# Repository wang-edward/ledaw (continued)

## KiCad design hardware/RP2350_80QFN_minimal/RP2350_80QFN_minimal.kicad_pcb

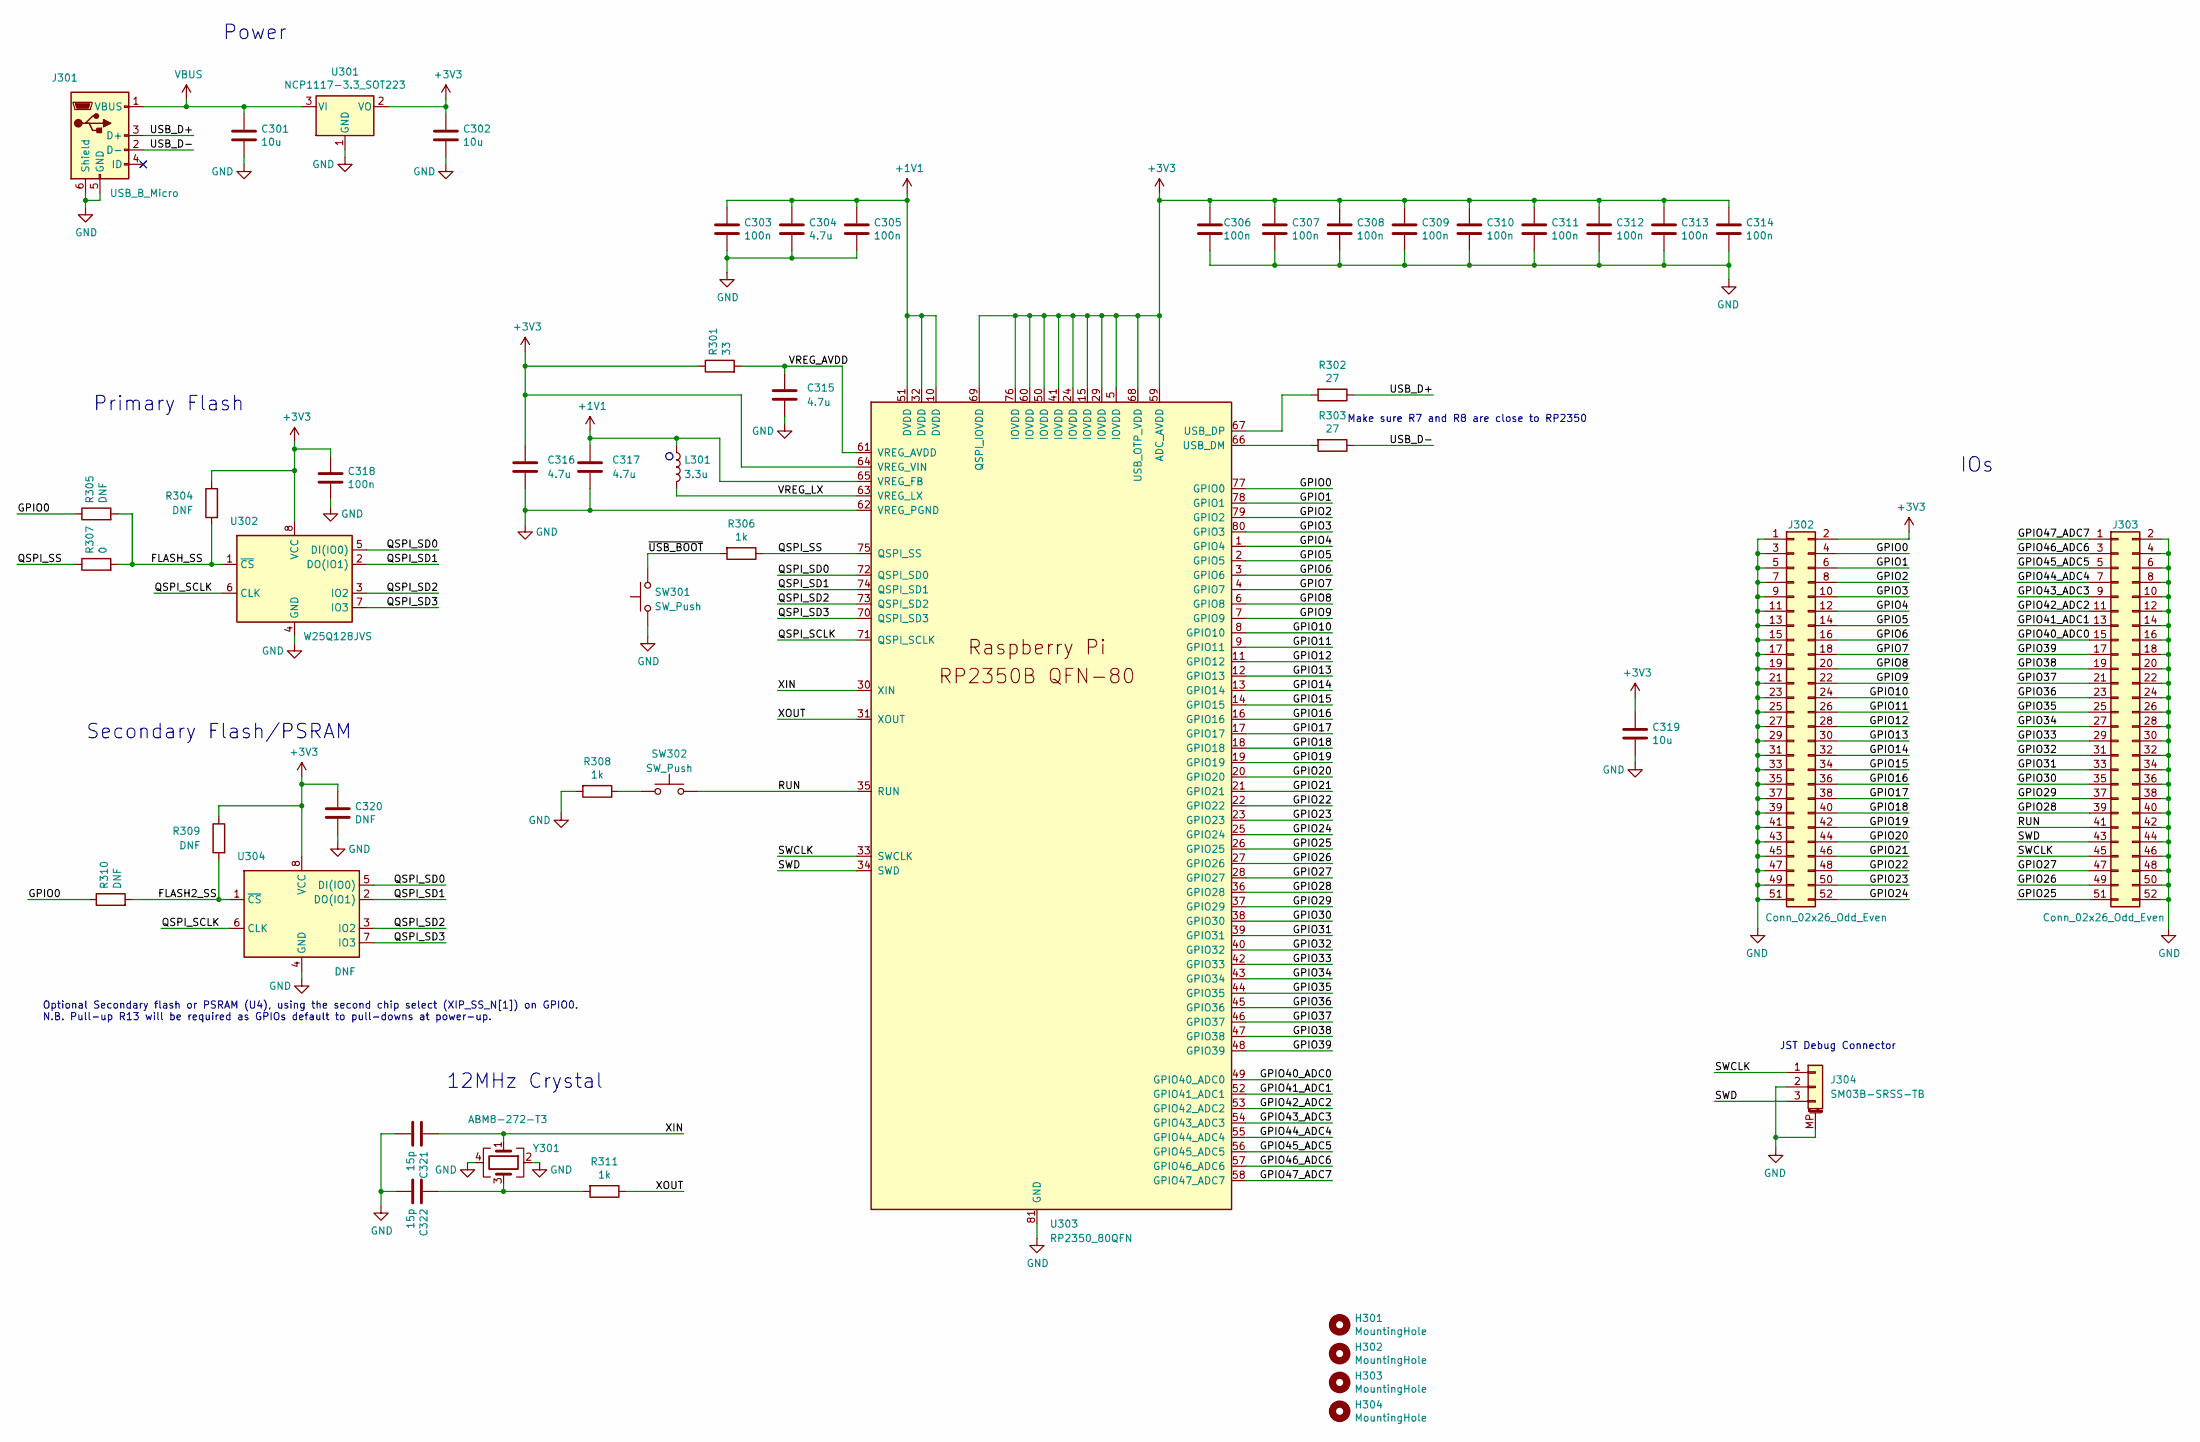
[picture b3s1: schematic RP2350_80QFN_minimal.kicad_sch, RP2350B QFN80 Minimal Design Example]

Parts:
C301, C302, C319: 10u; C_0805_2012Metric
C303, C305, C306, C307, C308, C309, C310, C311, C312, C313, C314, C318: 100n; C_0402_1005Metric
C304, C315: 4.7u; C_0402_1005Metric
C316, C317: 4.7u; C_0402_1005Metric_small_pads
C320: DNF; C_0402_1005Metric
C321, C322: 15p; C_0402_1005Metric
H301, H302, H303, H304: MountingHole; MountingHole_2.7mm_M2.5
J301: USB_B_Micro; USB_Micro-B_Amphenol_10103594-0001LF_Horizontal
J302, J303: Conn_02x26_Odd_Even; PinHeader_2x26_P2.54mm_Vertical
J304: SM03B-SRSS-TB; JST_SH_SM03B-SRSS-TB_1x03-1MP_P1.00mm_Horizontal
L301: 3.3u; L_pol_2016
R301: 33; R_0402_1005Metric
R302, R303: 27; R_0402_1005Metric
R304, R305, R309, R310: DNF; R_0402_1005Metric
R306, R308, R311: 1k; R_0402_1005Metric
R307: 0; R_0402_1005Metric
SW301, SW302: SW_Push; SW_Push_1P1T_NO_Vertical_Wuerth_434133025816
U301: NCP1117-3.3_SOT223; SOT-223-3_TabPin2
U302: W25Q128JVS; SOIC-8_5.23x5.23mm_P1.27mm
U303: RP2350_80QFN; RP2350-QFN-80-1EP_10x10_P0.4mm_EP3.4x3.4mm_ThermalVias
U304: DNF; SOIC-8_5.23x5.23mm_P1.27mm
Y301: ABM8-272-T3; Crystal_SMD_3225-4Pin_3.2x2.5mm

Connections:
+1V1: C303.1, C304.1, C305.1, C317.1, L301.1, U303.10 (DVDD), U303.32 (DVDD), U303.51 (DVDD), U303.65 (VREG_FB)
+3V3: C302.1, C306.1, C307.1, C308.1, C309.1, C310.1, C311.1, C312.1, C313.1, C314.1, C316.1, C318.1, C319.1, C320.1, J302.2, R301.1, R304.1, R309.1, U301.2 (VO), U302.8 (VCC), U303.5 (IOVDD), U303.15 (IOVDD), U303.24 (IOVDD), U303.29 (IOVDD), U303.41 (IOVDD), U303.50 (IOVDD), U303.59 (ADC_AVDD), U303.60 (IOVDD), U303.64 (VREG_VIN), U303.68 (USB_OTP_VDD), U303.69 (QSPI_IOVDD), U303.76 (IOVDD), U304.8 (VCC)
/FLASH2_SS: R309.2, R310.2, U304.1 (~CS)
/FLASH_SS: R304.2, R305.2, R307.2, U302.1 (~CS)
/GPIO0: J302.4, R305.1, R310.1, U303.77 (GPIO0)
/GPIO1: J302.6, U303.78 (GPIO1)
/GPIO2: J302.8, U303.79 (GPIO2)
/GPIO3: J302.10, U303.80 (GPIO3)
/GPIO4: J302.12, U303.1 (GPIO4)
/GPIO5: J302.14, U303.2 (GPIO5)
/GPIO6: J302.16, U303.3 (GPIO6)
/GPIO7: J302.18, U303.4 (GPIO7)
/GPIO8: J302.20, U303.6 (GPIO8)
/GPIO9: J302.22, U303.7 (GPIO9)
/GPIO10: J302.24, U303.8 (GPIO10)
/GPIO11: J302.26, U303.9 (GPIO11)
/GPIO12: J302.28, U303.11 (GPIO12)
/GPIO13: J302.30, U303.12 (GPIO13)
/GPIO14: J302.32, U303.13 (GPIO14)
/GPIO15: J302.34, U303.14 (GPIO15)
/GPIO16: J302.36, U303.16 (GPIO16)
/GPIO17: J302.38, U303.17 (GPIO17)
/GPIO18: J302.40, U303.18 (GPIO18)
/GPIO19: J302.42, U303.19 (GPIO19)
/GPIO20: J302.44, U303.20 (GPIO20)
/GPIO21: J302.46, U303.21 (GPIO21)
/GPIO22: J302.48, U303.22 (GPIO22)
/GPIO23: J302.50, U303.23 (GPIO23)
/GPIO24: J302.52, U303.25 (GPIO24)
/GPIO25: J303.51, U303.26 (GPIO25)
/GPIO26: J303.49, U303.27 (GPIO26)
/GPIO27: J303.47, U303.28 (GPIO27)
/GPIO28: J303.39, U303.36 (GPIO28)
/GPIO29: J303.37, U303.37 (GPIO29)
/GPIO30: J303.35, U303.38 (GPIO30)
/GPIO31: J303.33, U303.39 (GPIO31)
/GPIO32: J303.31, U303.40 (GPIO32)
/GPIO33: J303.29, U303.42 (GPIO33)
/GPIO34: J303.27, U303.43 (GPIO34)
/GPIO35: J303.25, U303.44 (GPIO35)
/GPIO36: J303.23, U303.45 (GPIO36)
/GPIO37: J303.21, U303.46 (GPIO37)
/GPIO38: J303.19, U303.47 (GPIO38)
/GPIO39: J303.17, U303.48 (GPIO39)
/GPIO40_ADC0: J303.15, U303.49 (GPIO40_ADC0)
/GPIO41_ADC1: J303.13, U303.52 (GPIO41_ADC1)
/GPIO42_ADC2: J303.11, U303.53 (GPIO42_ADC2)
/GPIO43_ADC3: J303.9, U303.54 (GPIO43_ADC3)
/GPIO44_ADC4: J303.7, U303.55 (GPIO44_ADC4)
/GPIO45_ADC5: J303.5, U303.56 (GPIO45_ADC5)
/GPIO46_ADC6: J303.3, U303.57 (GPIO46_ADC6)
/GPIO47_ADC7: J303.1, U303.58 (GPIO47_ADC7)
/QSPI_SCLK: U302.6 (CLK), U303.71 (QSPI_SCLK), U304.6 (CLK)
/QSPI_SD0: U302.5 (DI(IO0)), U303.72 (QSPI_SD0), U304.5 (DI(IO0))
/QSPI_SD1: U302.2 (DO(IO1)), U303.74 (QSPI_SD1), U304.2 (DO(IO1))
/QSPI_SD2: U302.3 (IO2), U303.73 (QSPI_SD2), U304.3 (IO2)
/QSPI_SD3: U302.7 (IO3), U303.70 (QSPI_SD3), U304.7 (IO3)
/QSPI_SS: R306.1, R307.1, U303.75 (QSPI_SS)
/RUN: J303.41, SW302.2, U303.35 (RUN)
/SWCLK: J303.45, J304.1, U303.33 (SWCLK)
/SWD: J303.43, J304.3, U303.34 (SWD)
/USB_D+: J301.3 (D+), R302.1
/USB_D-: J301.2 (D-), R303.1
/VREG_AVDD: C315.1, R301.2, U303.61 (VREG_AVDD)
/VREG_LX: L301.2, U303.63 (VREG_LX)
/XIN: C321.1, U303.30 (XIN), Y301.1
/XOUT: R311.1, U303.31 (XOUT)
/~USB_BOOT: R306.2, SW301.2
GND: C301.2, C302.2, C303.2, C304.2, C305.2, C306.2, C307.2, C308.2, C309.2, C310.2, C311.2, C312.2, C313.2, C314.2, C315.2, C316.2, C317.2, C318.2, C319.2, C320.2, C321.2, C322.2, J301.5 (GND), J301.6 (Shield), J302.1, J302.3, J302.5, J302.7, J302.9, J302.11, J302.13, J302.15, J302.17, J302.19, J302.21, J302.23, J302.25, J302.27, J302.29, J302.31, J302.33, J302.35, J302.37, J302.39, J302.41, J302.43, J302.45, J302.47, J302.49, J302.51, J303.2, J303.4, J303.6, J303.8, J303.10, J303.12, J303.14, J303.16, J303.18, J303.20, J303.22, J303.24, J303.26, J303.28, J303.30, J303.32, J303.34, J303.36, J303.38, J303.40, J303.42, J303.44, J303.46, J303.48, J303.50, J303.52, J304.2, J304.MP (MountPin), R308.2, SW301.1, U301.1 (GND), U302.4 (GND), U303.62 (VREG_PGND), U303.81 (GND), U304.4 (GND), Y301.2, Y301.4
unnamed: C322.1, R311.2, Y301.3
unnamed: R308.1, SW302.1
unnamed: R303.2, U303.66 (USB_DM)
unnamed: R302.2, U303.67 (USB_DP)
VBUS: C301.1, J301.1 (VBUS), U301.3 (VI)

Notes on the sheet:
Optional Secondary flash or PSRAM (U4), using the second chip select (XIP_SS_N[1]) on GPIO0. N.B. Pull-up R13 will be required as GPIOs default to pull-downs at power-up.
IOs
12MHz Crystal
Primary Flash
JST Debug Connector
Make sure R7 and R8 are close to RP2350
Secondary Flash/PSRAM
Power

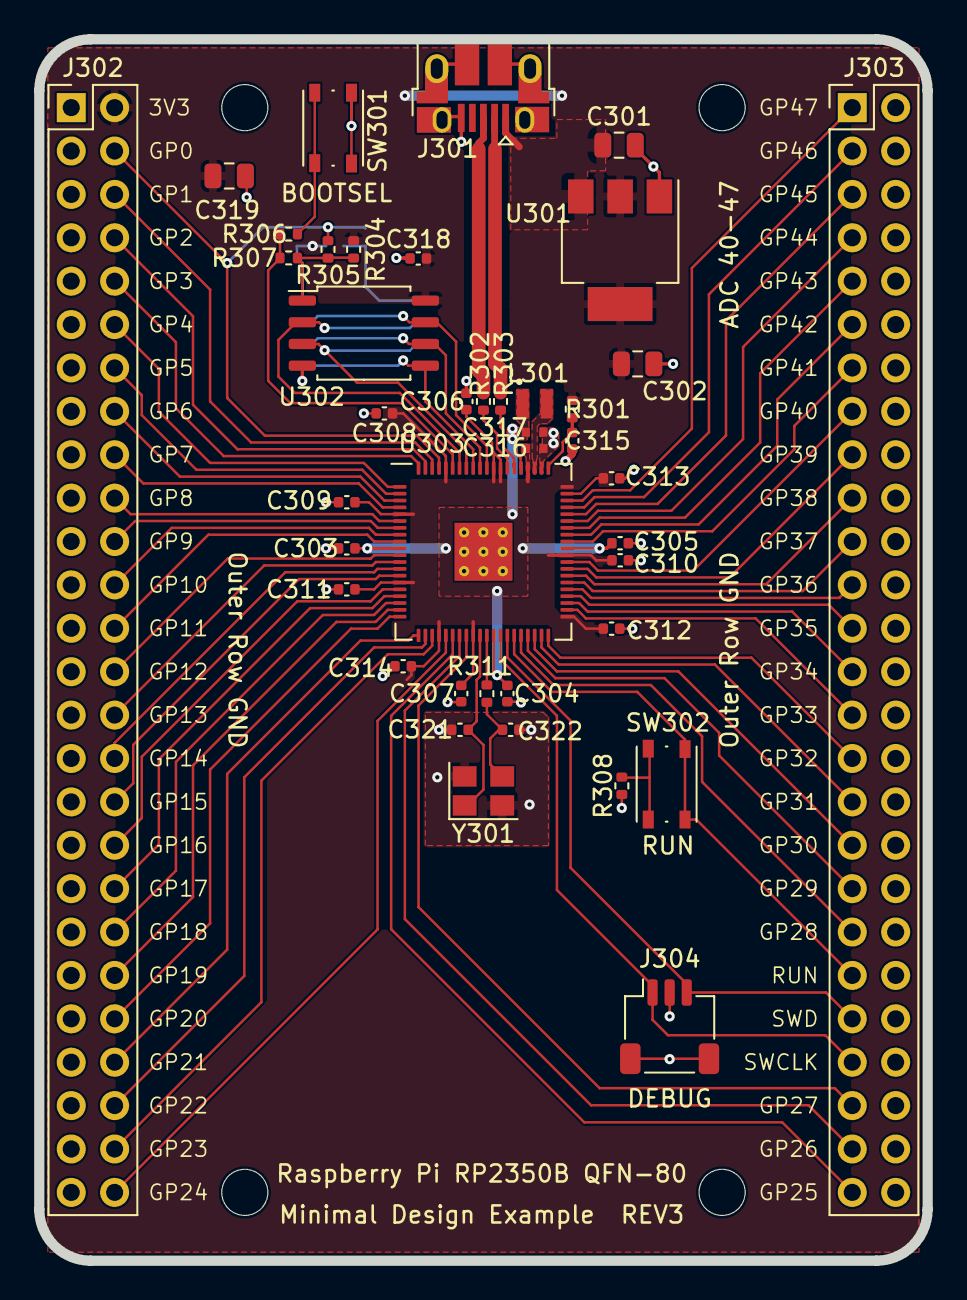
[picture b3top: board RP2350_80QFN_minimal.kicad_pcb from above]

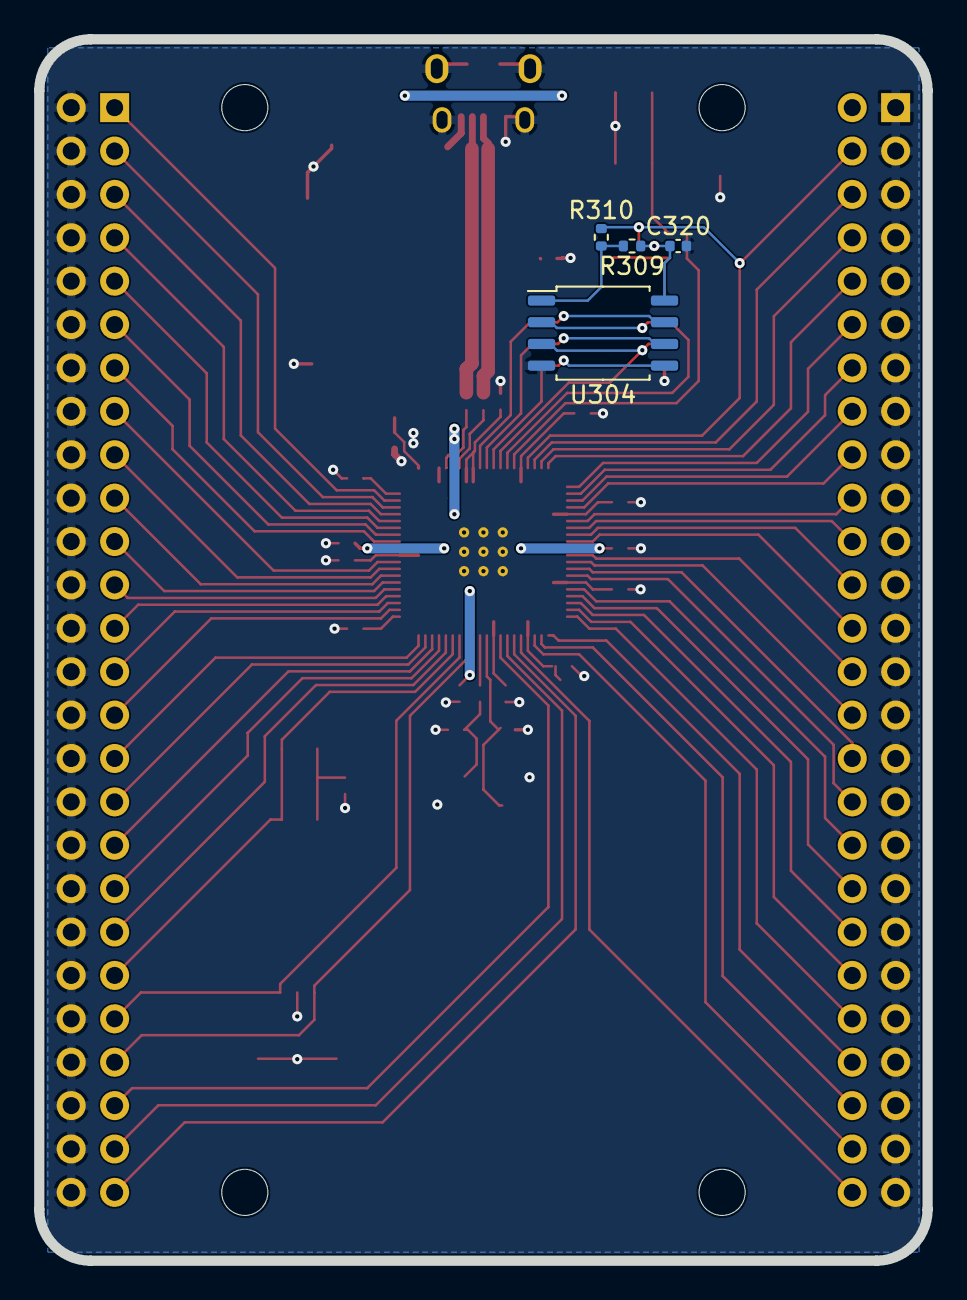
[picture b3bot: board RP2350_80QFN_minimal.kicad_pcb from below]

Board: 2 copper layers, 52.0 x 71.5 mm, 49 parts (4 on the bottom side), 74 nets.

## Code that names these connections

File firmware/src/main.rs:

#![no_std]
#![no_main]

use core::fmt::Write as _;
use defmt::info;
use defmt_rtt as _;
use embedded_hal::digital::{InputPin, OutputPin};
use hal::uart::{DataBits, StopBits, UartConfig, UartPeripheral};
use panic_probe as _;
use rp235x_hal::clocks::init_clocks_and_plls;
use rp235x_hal::fugit::RateExtU32;
use rp235x_hal::{self as hal, entry};
use rp235x_hal::{Clock, pac};

// Provide an alias for our BSP so we can switch targets quickly.
// Uncomment the BSP you included in Cargo.toml, the rest of the code does not need to change.
// use some_bsp;

/// Tell the Boot ROM about our application
#[unsafe(link_section = ".start_block")]
#[used]
pub static IMAGE_DEF: hal::block::ImageDef = hal::block::ImageDef::secure_exe();

#[entry]
fn main() -> ! {
    info!("Program start");
    let mut pac = pac::Peripherals::take().unwrap();
    let core = cortex_m::Peripherals::take().unwrap();
    let mut watchdog = hal::Watchdog::new(pac.WATCHDOG);
    let sio = hal::Sio::new(pac.SIO);

    // External high-speed crystal on the pico board is 12Mhz
    let external_xtal_freq_hz = 12_000_000u32;
    let clocks = init_clocks_and_plls(
        external_xtal_freq_hz,
        pac.XOSC,
        pac.CLOCKS,
        pac.PLL_SYS,
        pac.PLL_USB,
        &mut pac.RESETS,
        &mut watchdog,
    )
    .ok()
    .unwrap();

    let mut delay = cortex_m::delay::Delay::new(core.SYST, clocks.system_clock.freq().to_Hz());

    let pins = hal::gpio::Pins::new(
        pac.IO_BANK0,
        pac.PADS_BANK0,
        sio.gpio_bank0,
        &mut pac.RESETS,
    );

    let uart_pins = (pins.gpio0.into_function(), pins.gpio1.into_function());
    let mut uart = UartPeripheral::new(pac.UART0, uart_pins, &mut pac.RESETS)
        .enable(
            UartConfig::new(115_200u32.Hz(), DataBits::Eight, None, StopBits::One),
            clocks.peripheral_clock.freq(),
        )
        .unwrap();

    // Rows are active high and idle rows are low so only the selected row can raise a column.
    let mut rows = [
        pins.gpio16.into_push_pull_output().into_dyn_pin(),
        pins.gpio17.into_push_pull_output().into_dyn_pin(),
        pins.gpio18.into_push_pull_output().into_dyn_pin(),
    ];
    for row in &mut rows {
        row.set_low().unwrap();
    }

    let mut columns = [
        pins.gpio32.into_pull_down_input().into_dyn_pin(),
        pins.gpio31.into_pull_down_input().into_dyn_pin(),
        pins.gpio30.into_pull_down_input().into_dyn_pin(),
        pins.gpio29.into_pull_down_input().into_dyn_pin(),
        pins.gpio28.into_pull_down_input().into_dyn_pin(),
        pins.gpio27.into_pull_down_input().into_dyn_pin(),
        pins.gpio26.into_pull_down_input().into_dyn_pin(),
        pins.gpio25.into_pull_down_input().into_dyn_pin(),
        pins.gpio24.into_pull_down_input().into_dyn_pin(),
        pins.gpio23.into_pull_down_input().into_dyn_pin(),
        pins.gpio22.into_pull_down_input().into_dyn_pin(),
        pins.gpio21.into_pull_down_input().into_dyn_pin(),
        pins.gpio20.into_pull_down_input().into_dyn_pin(),
        pins.gpio19.into_pull_down_input().into_dyn_pin(),
    ];
    let mut previous = [u16::MAX; 3];

    loop {
        let mut scan = [0u16; 3];

        for (row_index, row) in rows.iter_mut().enumerate() {
            row.set_high().unwrap();
            delay.delay_us(5);

            for (column_index, column) in columns.iter_mut().enumerate() {
                if column.is_high().unwrap() {
                    scan[row_index] |= 1 << column_index;
                }
            }

            row.set_low().unwrap();
        }

        if scan != previous {
            // Each bit is a pressed key; bit 0 is GPIO32 and bit 13 is GPIO19.
            info!(
                "matrix: {=u16:04x} {=u16:04x} {=u16:04x}",
                scan[0], scan[1], scan[2]
            );
            // send over uart (mostly as a test)
            write!(
                uart,
                "matrix: {:04x} {:04x} {:04x}\r\n",
                scan[0], scan[1], scan[2]
            )
            .unwrap();
            previous = scan;
        }

        delay.delay_ms(1);
    }
}

/// Program metadata for `picotool info`
#[unsafe(link_section = ".bi_entries")]
#[used]
pub static PICOTOOL_ENTRIES: [rp235x_hal::binary_info::EntryAddr; 5] = [
    rp235x_hal::binary_info::rp_cargo_bin_name!(),
    rp235x_hal::binary_info::rp_cargo_version!(),
    rp235x_hal::binary_info::rp_program_description!(c"RP2350 Template"),
    rp235x_hal::binary_info::rp_cargo_homepage_url!(),
    rp235x_hal::binary_info::rp_program_build_attribute!(),
];

// End of file

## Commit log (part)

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2026-03-25 render in fuzz (#65)
2026-03-25 render cursor
2026-03-26 gpt socket examples
2026-03-26 add art build step
2026-03-26 retry socket 50 times
2026-03-26 uv build step
2026-03-26 zig as server, py as client, spawn py in zig
2026-03-26 use gpu (needs macos >= 14.0)
2026-03-26 easyOcr instead
2026-03-26 clear_timeline
2026-03-26 wip integrating ledaw
2026-03-26 wip make read a thread
2026-03-31 wip render
2026-03-31 find camera using resolution
2026-03-31 render ocr output
2026-03-31 a and b?
2026-03-31 wip map space to esc, del, ent
2026-03-31 gpt factor out
2026-04-01 timespeed in fuzz
2026-04-02 use it
2026-04-02 less
2026-04-02 even less
2026-04-02 type
2026-04-02 Fuzz timemod (#75)
    * timespeed in fuzz
    * use it
    * less
    * even less
    * type
2026-04-02 set fuzz seed to currtime
2026-04-02 dont crash on underflow
2026-04-02 more frequent timeskip in fuzz
2026-04-02 remove track_idx from toggle_record
2026-04-02 red means recording, atomic
2026-04-02 fix crashes and push playhead less
2026-04-02 wip fix art segf
2026-04-02 wacky AI pixel code
2026-04-02 fix app.init
2026-04-02 b => .overview
2026-04-02 render notes
2026-04-02 cleanups
2026-04-02 add set {record, play}
2026-04-02 tricks to make gen more interesting
2026-04-02 grid size 128
2026-04-02 phaser
2026-04-02 max plugins 2 and add check in audiothread
2026-04-02 lighting spell for phaser
2026-04-02 random index to plugin selecta
2026-04-02 some tuuuuuuuuuuuuning
2026-04-02 synth controls!!!!!!
2026-04-08 fullscreen
2026-04-23 midi clips (#420)
    render notes
    draw different colors
2026-04-24 clean
2026-05-07 Revert "midi clips (#420)"
    This reverts commit 5dad6255bc991d015f7382cc5a292728bb1aea8a.
2026-05-07 revert++
2026-05-07 gles 2
2026-05-08 test_display
2026-05-08 target
2026-05-08 typo
2026-05-10 hw: lemme get it started
2026-05-13 hw: headphone and wip mic
2026-05-19 hw: big simplification
2026-05-20 hw: speakers, line in/out. only missing digital mic now
2026-05-20 hw: done codec?
2026-05-20 hw:hat
2026-05-20 hw: really close!!
2026-05-21 hw: assign
2026-05-21 hw: sync
2026-05-21 hw: delete ledaw
2026-05-23 hw: placement
2026-05-24 upload dru
2026-05-24 place all components
2026-05-26 bypass cap
2026-06-03 all signal except ID chip
2026-06-03 all signals
2026-06-03 lil groundfil
2026-06-03 some troll power planes
2026-06-04 vias for planes
2026-06-05 before drc
2026-06-05 done?
2026-06-09 restore backup from June 6 1:34 AM
2026-06-18 lock ports
2026-06-21 big build changes
2026-06-21 oled
2026-06-22 init
2026-06-22 many
2026-06-22 u8 show
2026-06-22 Oled (#89)
    * init
    * a
    * b
    * c
    * d
    * e
2026-06-22 structure
2026-06-23 submodule
2026-06-23 config
2026-06-23 Revert "submodule"
    This reverts commit 6cd2e97f5381664ff20fb04ace3b7d99cfa5faa6.
2026-06-23 my submod
2026-06-23 link gles libs on hw
2026-06-23 dont depend on everything?
2026-06-23 update submodule
2026-06-23 del my ting
2026-06-23 guard HW
2026-06-23 dont depend on everything everytime
2026-06-23 leOS (#92)
    * structure
    * submodule
    * config
    * Revert "submodule"
    This reverts commit 6cd2e97f5381664ff20fb04ace3b7d99cfa5faa6.
    * my submod
2026-06-26 BOARD: LET ME GET IT STARTED BB WITH THE ROBIN LOOKING ALL EDWARD WANG
2026-06-26 ports and shieeet
2026-06-28 some 3d models
2026-06-28 diff dc and rst
2026-06-28 find correct device
2026-06-28 list
2026-06-28 more?
2026-06-29 update ref to libsoundio
2026-06-29 default device?
2026-06-29 print on must
2026-06-29 kill g_run_audio instead of panicking
2026-06-29 rst actually gpio6
2026-06-29 update oled dc and rst pins (#98)
    * diff dc and rst
    * rst actually gpio6
2026-06-29 fix device search
2026-06-29 try hw
2026-06-29 back
